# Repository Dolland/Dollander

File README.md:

# Handheld Gaming Console - Master Degree Thesis

As for the title, this project is my Electronics Engineering Master Thesis.
This is a handheld console based on Raspberry Pi Zero 2.

## HOW IT BEGAN

I started working on this idea some years ago and came up designing a console like in the photo:

*FOTO*

As you can see, this was a serious wires mess, but it worked! (actually it still works)
For the first prototipe I used ready-to-use boards for supply, audio, ADC and so on.
The screen was a Composite 5" retro camera 12V display (really bad quality).
The shell was entirely designed from scratch.

## HOW IT BECAME

After a year of use, i decided that this project deserved more attention and started thinking about a custom PCB that would integrate all the components needed for power supply, audio amplification, ADC, display driving etc.
I've designed the PMIC stage, as well as the display interfacing and all the other stuffs.
The PCB finally come out like this:

The console now has a 5" RGB Parallel Interface display driven by a HDMI-to-TTL converter that receives the HDMI signal from a HDMI switch, that in turn manages to switch the output between the internal display and the HDMI external port.

The console has an analog stick, 4 dorsal buttons, 14 front buttons, a speaker (but the PCB supports two speakers), a full-size HDMI output port, a USB-C charging port and a plenty of internal space for Li-Ion cells (i use a 3000mAh one but you can use bigger ones).

This project is by all means not perfect, some things are missing (backlight adjustment is supported by hardware but not implemented in the PCB) and surely the next PCB revision will be more compact (and so cheaper to order) but it works really well.

The design of the shell and the buttons was done in TinkerCAD (what an awful choice) because well, i only know this tool, but surely the next step should be porting all the CAD files into a more professional CAD (Fusion?)

Here is the top printing:

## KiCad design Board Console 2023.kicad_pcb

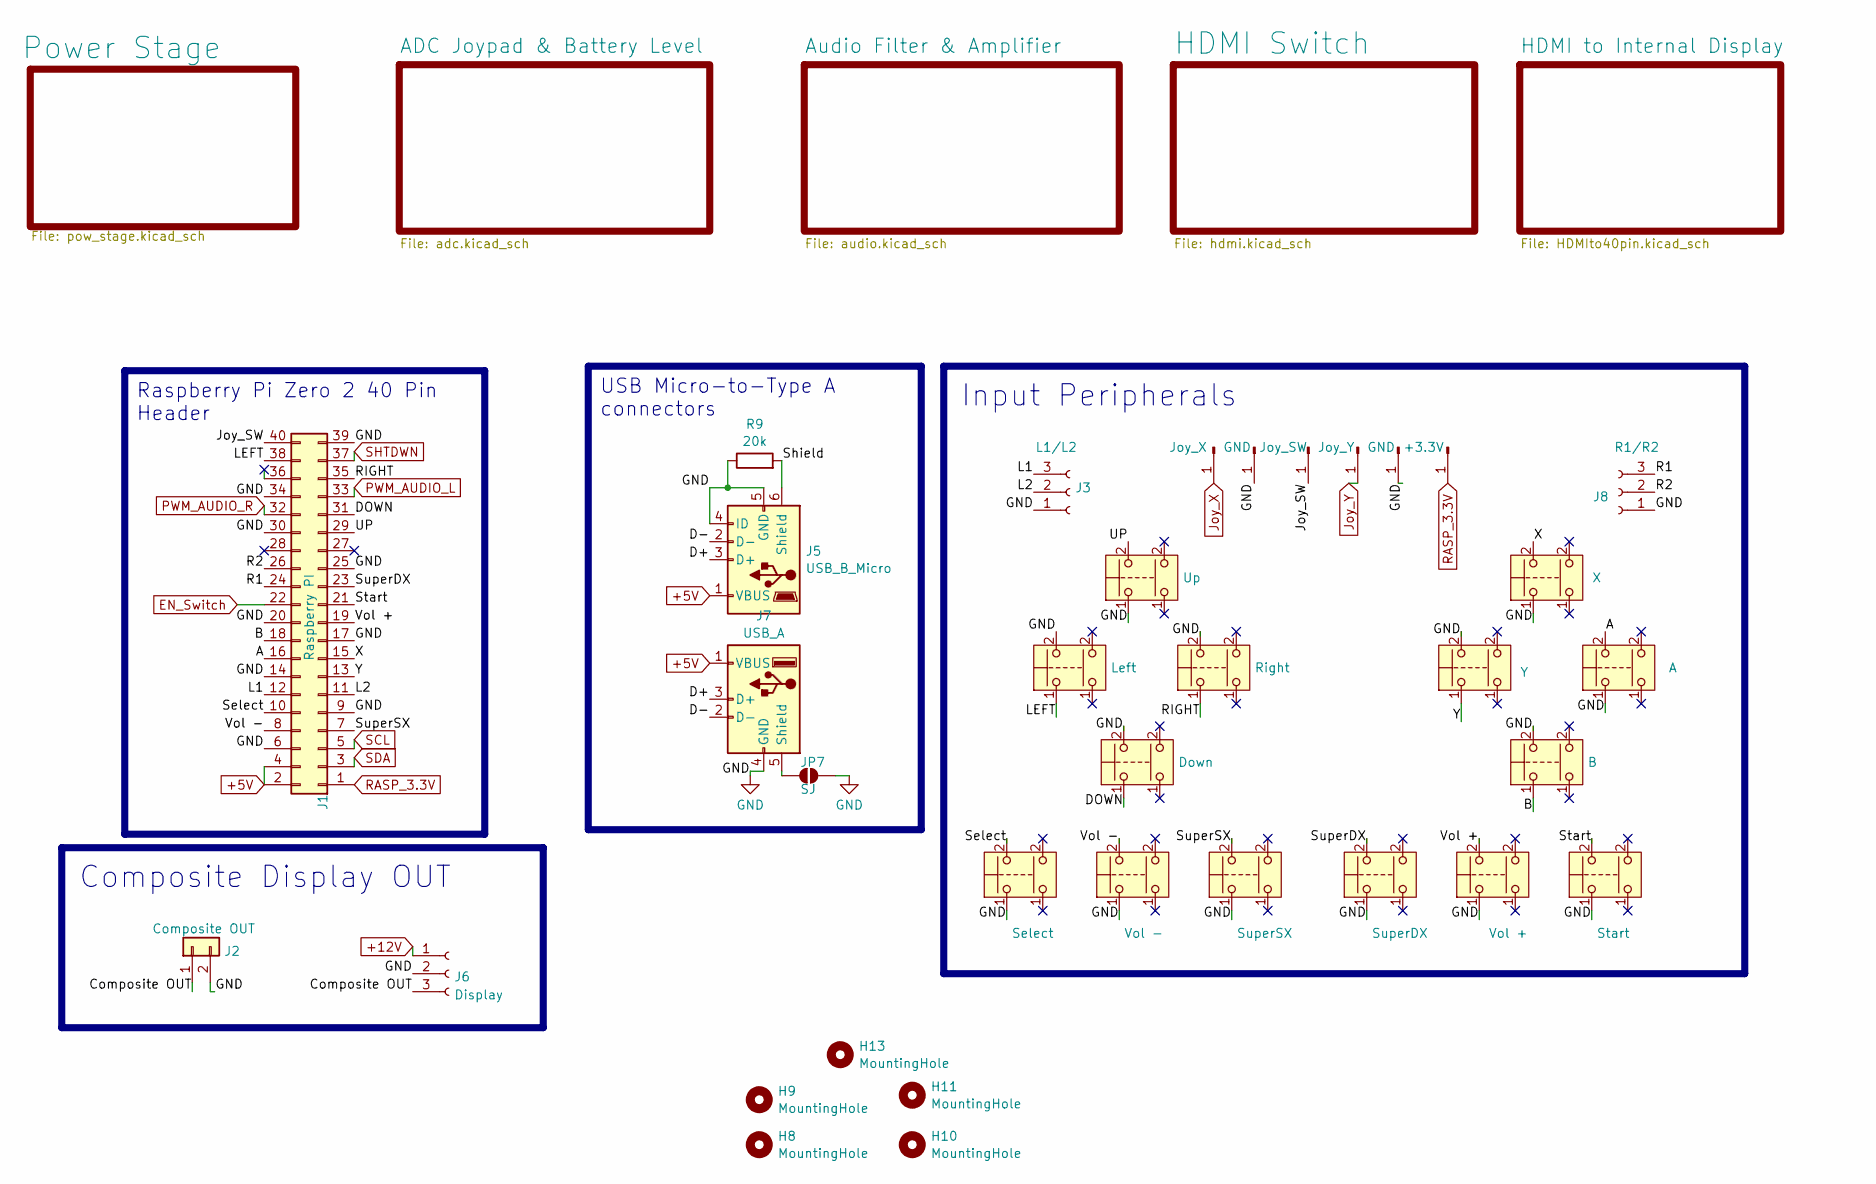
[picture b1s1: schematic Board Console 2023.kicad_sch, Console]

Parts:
H1: Joy_X; TestPoint_Pad_0.8x2.8
H2, H5: GND; TestPoint_Pad_0.8x2.8
H3: Joy_SW; TestPoint_Pad_0.8x2.8
H4: Joy_Y; TestPoint_Pad_0.8x2.8
H6: +3.3V; TestPoint_Pad_0.8x2.8
H8, H9, H10, H11, H13: MountingHole; MountingHole_2.2mm_M2
J1: Raspberry PI; Raspberry_Pi_Zero_Socketed_THT_FaceUp_MountingHoles
J2: Composite OUT; PinHeader_1x02_P2.00mm_Vertical
J3: L1/L2; PinHeader_1x03_P2.54mm_Vertical
J5: USB_B_Micro; USB_Micro-B_Amphenol_10118194_Horizontal
J6: Display; PinHeader_1x03_P2.54mm_Vertical
J7: USB_A; AMPHENOL_UE27AC5410H
J8: R1/R2; PinHeader_1x03_P2.54mm_Vertical
JP7: SJ; SolderJumper-2_P1.3mm_Open_Pad1.0x1.5mm
R9: 20k; R_0603_1608Metric_Pad0.98x0.95mm_HandSolder
SW3: Vol -; SW_Push_1P1T_NO_6x6mm_H9.5mm
SW4: SuperSX; SW_Push_1P1T_NO_6x6mm_H9.5mm
SW5: Select; SW_Push_1P1T_NO_6x6mm_H9.5mm
SW6: Vol +; SW_Push_1P1T_NO_6x6mm_H9.5mm
SW7: Start; SW_Push_1P1T_NO_6x6mm_H9.5mm
SW8: B; SW_Push_1P1T_NO_6x6mm_H9.5mm
SW9: Y; SW_Push_1P1T_NO_6x6mm_H9.5mm
SW10: A; SW_Push_1P1T_NO_6x6mm_H9.5mm
SW11: X; SW_Push_1P1T_NO_6x6mm_H9.5mm
SW12: Down; SW_Push_1P1T_NO_6x6mm_H9.5mm
SW13: Left; SW_Push_1P1T_NO_6x6mm_H9.5mm
SW14: Up; SW_Push_1P1T_NO_6x6mm_H9.5mm
SW15: Right; SW_Push_1P1T_NO_6x6mm_H9.5mm
SW17: SuperDX; SW_Push_1P1T_NO_6x6mm_H9.5mm

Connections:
+5V: J1.2, J1.4, J5.1 (VBUS), J7.1 (VBUS); also elsewhere on the board
+12V: J6.1; also elsewhere on the board
/A: J1.16, SW10.2
/B: J1.18, SW8.1
/Composite OUT: J2.1, J6.3
/D+: J5.3 (D+), J7.3 (D+)
/D-: J5.2 (D-), J7.2 (D-)
/DOWN: J1.31, SW12.1
/Joy_SW: H3.1, J1.40
/L1: J1.12, J3.3
/L2: J1.11, J3.2
/LEFT: J1.38, SW13.1
/R1: J1.24, J8.3
/R2: J1.26, J8.2
/RIGHT: J1.35, SW15.1
/Select: J1.10, SW5.2
/Shield: J5.6 (Shield), R9.2
/Start: J1.21, SW7.2
/SuperDX: J1.23, SW17.2
/SuperSX: J1.7, SW4.2
/UP: J1.29, SW14.2
/Vol +: J1.19, SW6.2
/Vol -: J1.8, SW3.2
/X: J1.15, SW11.2
/Y: J1.13, SW9.1
EN_Switch: J1.22; also elsewhere on the board
GND: H2.1, H5.1, J1.6, J1.9, J1.14, J1.17, J1.20, J1.25, J1.30, J1.34, J1.39, J2.2, J3.1, J5.4 (ID), J5.5 (GND), J6.2, J7.4 (GND), J8.1, JP7.1 (A), R9.1, SW3.1, SW4.1, SW5.1, SW6.1, SW7.1, SW8.2, SW9.2, SW10.1, SW11.1, SW12.2, SW13.2, SW14.1, SW15.2, SW17.1; also elsewhere on the board
Joy_X: H1.1; also elsewhere on the board
Joy_Y: H4.1; also elsewhere on the board
unnamed: J7.5 (Shield), JP7.2 (B)
PWM_AUDIO_L: J1.33; also elsewhere on the board
PWM_AUDIO_R: J1.32; also elsewhere on the board
RASP_3.3V: H6.1, J1.1; also elsewhere on the board
SCL: J1.5; also elsewhere on the board
SDA: J1.3; also elsewhere on the board
SHTDWN: J1.37; also elsewhere on the board

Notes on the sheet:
Composite Display OUT
Raspberry Pi Zero 2 40 Pin Header
USB Micro-to-Type A connectors
Input Peripherals

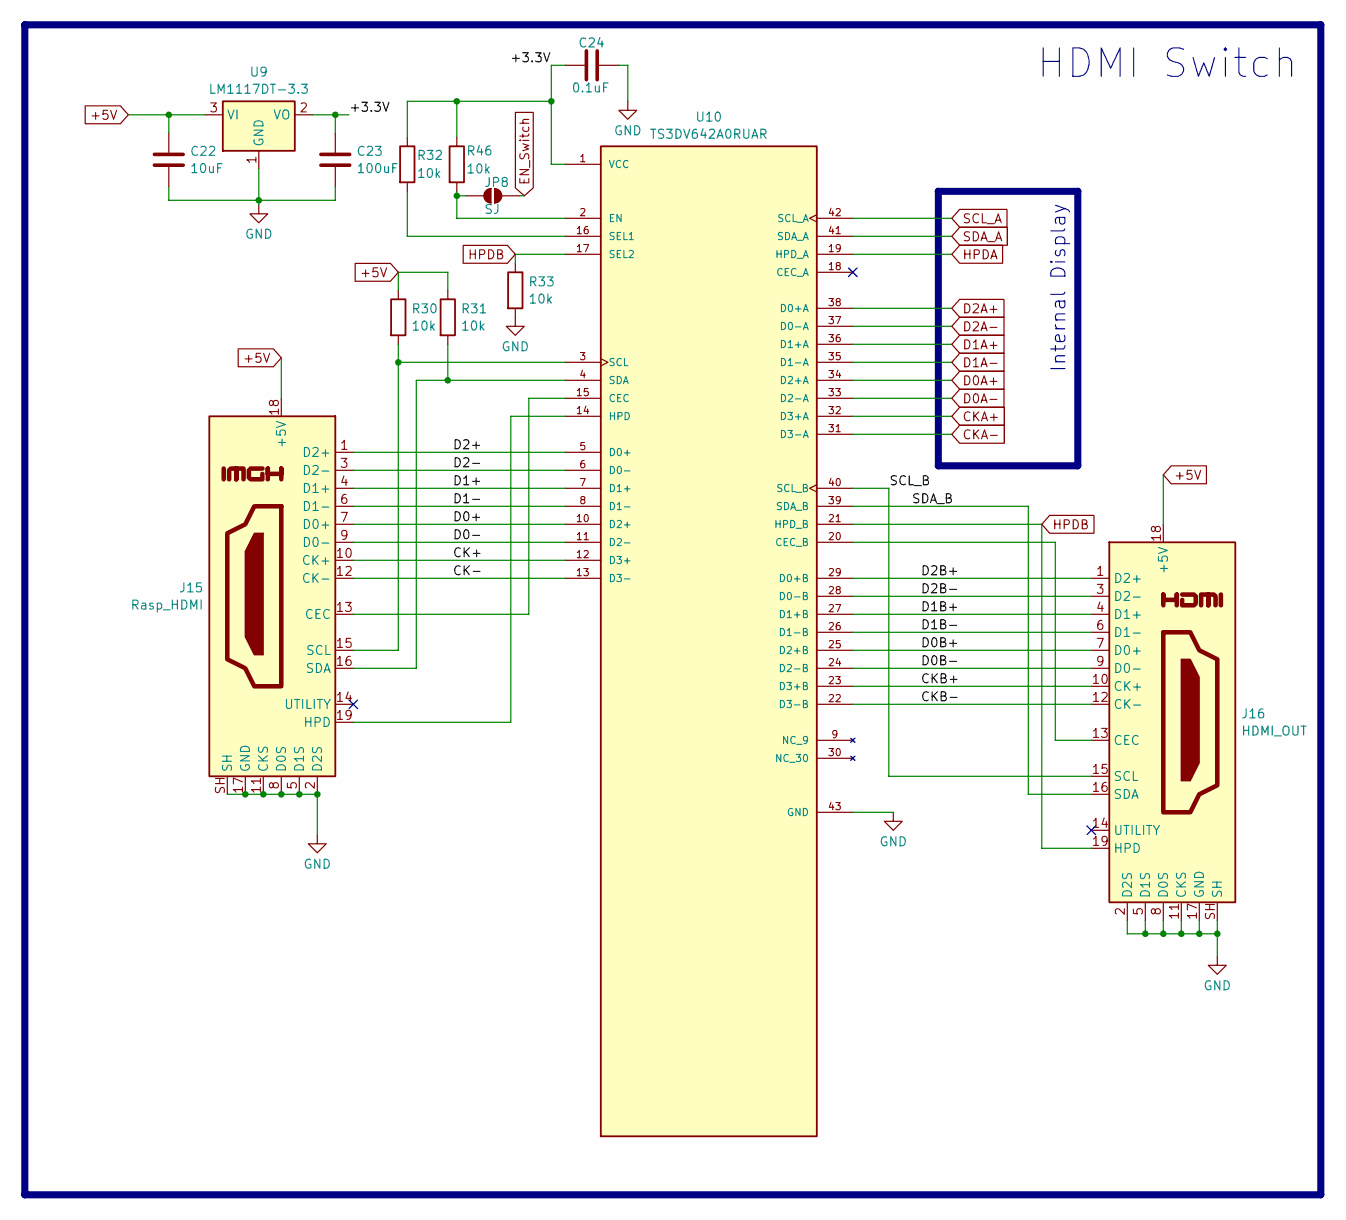
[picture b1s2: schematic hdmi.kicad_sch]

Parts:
C22: 10uF; C_0603_1608Metric_Pad1.08x0.95mm_HandSolder
C23: 100uF; C_1206_3216Metric_Pad1.33x1.80mm_HandSolder
C24: 0.1uF; C_0603_1608Metric_Pad1.08x0.95mm_HandSolder
J15: Rasp_HDMI; HDMI_A_Amphenol_10029449-x01xLF_Horizontal
J16: HDMI_OUT; HDMI_A_Amphenol_10029449-x01xLF_Horizontal
JP8: SJ; SolderJumper-2_P1.3mm_Open_Pad1.0x1.5mm
R30, R31, R32, R33, R46: 10k; R_0603_1608Metric_Pad0.98x0.95mm_HandSolder
U9: LM1117DT-3.3; SOT-223-3_TabPin2
U10: TS3DV642A0RUAR; QFN50P900X350X80-43N; PARTREV 4219139/A 03/2020

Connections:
+5V: C22.1, J15.18 (+5V), J16.18 (+5V), R30.1, R31.1, U9.3 (VI); also elsewhere on the board
/HDMI Switch/+3.3V: C23.1, C24.1, R32.1, R46.1, U9.2 (VO), U10.1 (VCC)
/HDMI Switch/CK+: J15.10 (CK+), U10.12 (D3+)
/HDMI Switch/CK-: J15.12 (CK-), U10.13 (D3-)
/HDMI Switch/CKB+: J16.10 (CK+), U10.23 (D3+B)
/HDMI Switch/CKB-: J16.12 (CK-), U10.22 (D3-B)
/HDMI Switch/D0+: J15.7 (D0+), U10.10 (D2+)
/HDMI Switch/D0-: J15.9 (D0-), U10.11 (D2-)
/HDMI Switch/D0B+: J16.7 (D0+), U10.25 (D2+B)
/HDMI Switch/D0B-: J16.9 (D0-), U10.24 (D2-B)
/HDMI Switch/D1+: J15.4 (D1+), U10.7 (D1+)
/HDMI Switch/D1-: J15.6 (D1-), U10.8 (D1-)
/HDMI Switch/D1B+: J16.4 (D1+), U10.27 (D1+B)
/HDMI Switch/D1B-: J16.6 (D1-), U10.26 (D1-B)
/HDMI Switch/D2+: J15.1 (D2+), U10.5 (D0+)
/HDMI Switch/D2-: J15.3 (D2-), U10.6 (D0-)
/HDMI Switch/D2B+: J16.1 (D2+), U10.29 (D0+B)
/HDMI Switch/D2B-: J16.3 (D2-), U10.28 (D0-B)
/HDMI Switch/SCL_B: J16.15 (SCL), U10.40 (SCL_B)
/HDMI Switch/SDA_B: J16.16 (SDA), U10.39 (SDA_B)
CKA+: U10.32 (D3+A); also elsewhere on the board
CKA-: U10.31 (D3-A); also elsewhere on the board
D0A+: U10.34 (D2+A); also elsewhere on the board
D0A-: U10.33 (D2-A); also elsewhere on the board
D1A+: U10.36 (D1+A); also elsewhere on the board
D1A-: U10.35 (D1-A); also elsewhere on the board
D2A+: U10.38 (D0+A); also elsewhere on the board
D2A-: U10.37 (D0-A); also elsewhere on the board
EN_Switch: JP8.1 (A); also elsewhere on the board
GND: C22.2, C23.2, C24.2, J15.2 (D2S), J15.5 (D1S), J15.8 (D0S), J15.11 (CKS), J15.17 (GND), J15.SH, J16.2 (D2S), J16.5 (D1S), J16.8 (D0S), J16.11 (CKS), J16.17 (GND), J16.SH, R33.2, U9.1 (GND), U10.43 (GND); also elsewhere on the board
HPDA: U10.19 (HPD_A); also elsewhere on the board
HPDB: J16.19 (HPD), R33.1, U10.17 (SEL2), U10.21 (HPD_B)
unnamed: J15.13 (CEC), U10.15 (CEC)
unnamed: J15.19 (HPD), U10.14 (HPD)
unnamed: J15.15 (SCL), R30.2, U10.3 (SCL)
unnamed: J15.16 (SDA), R31.2, U10.4 (SDA)
unnamed: J16.13 (CEC), U10.20 (CEC_B)
unnamed: JP8.2 (B), R46.2, U10.2 (EN)
unnamed: R32.2, U10.16 (SEL1)
SCL_A: U10.42 (SCL_A); also elsewhere on the board
SDA_A: U10.41 (SDA_A); also elsewhere on the board

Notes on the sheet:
Internal Display
HDMI Switch

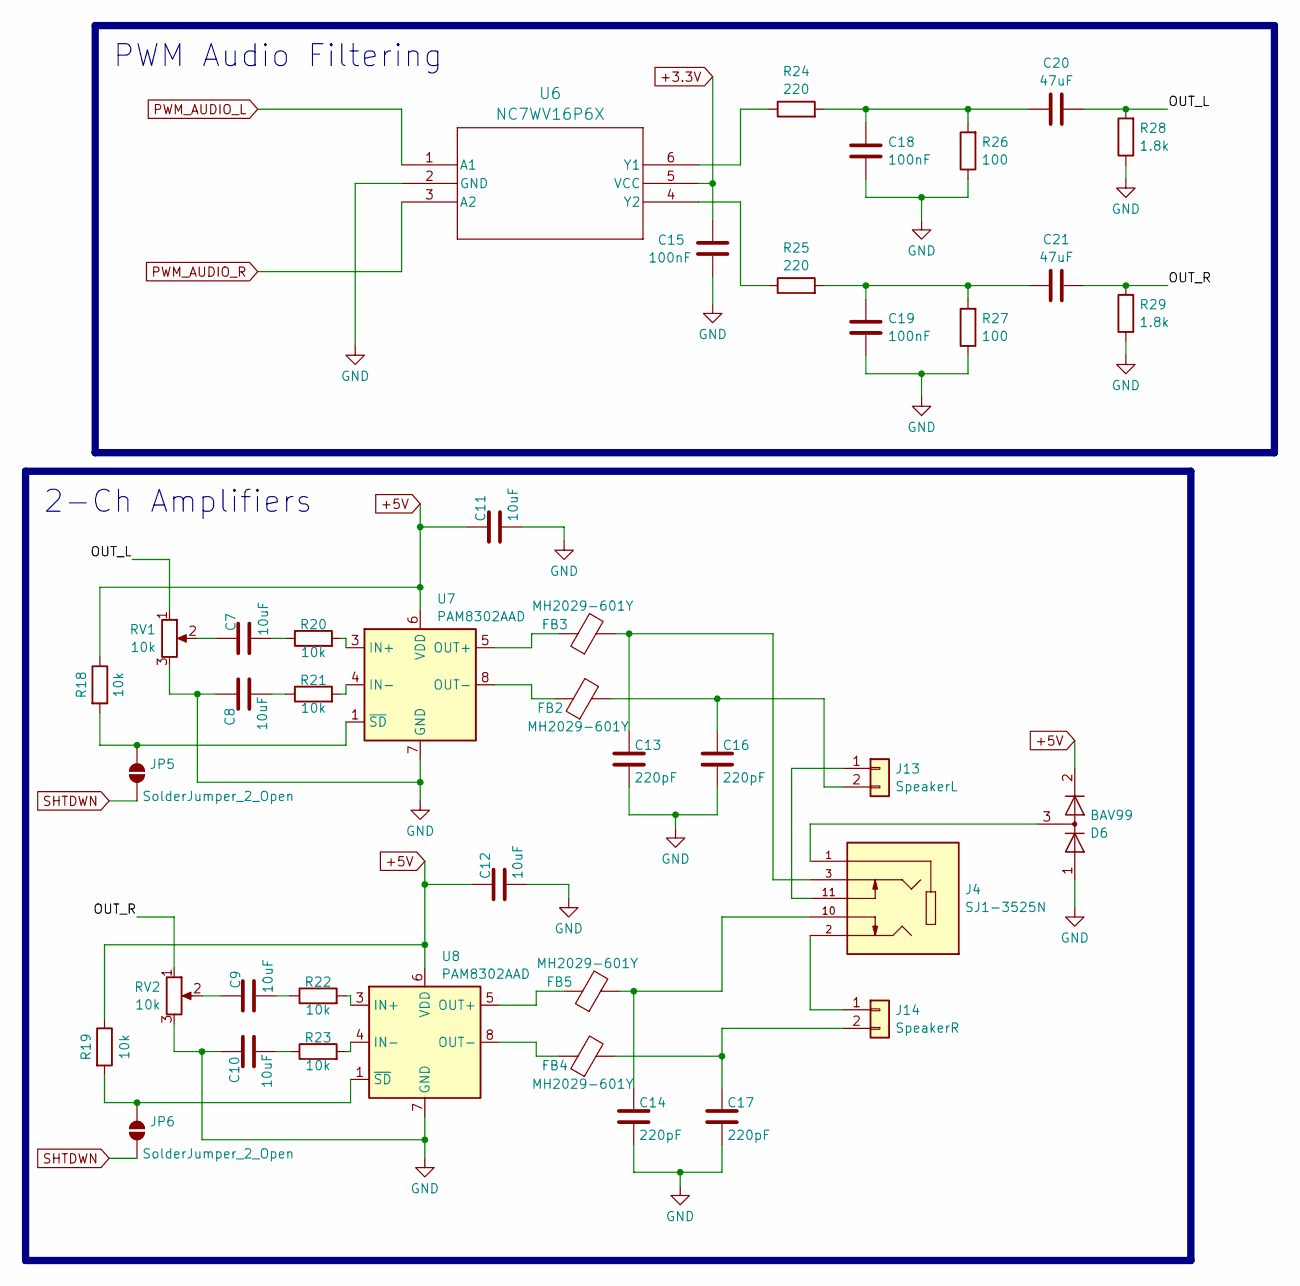
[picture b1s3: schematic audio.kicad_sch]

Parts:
C7, C8, C9, C10, C11, C12: 10uF; C_0603_1608Metric_Pad1.08x0.95mm_HandSolder
C13, C14, C16, C17: 220pF; C_0603_1608Metric_Pad1.08x0.95mm_HandSolder
C15, C18, C19: 100nF; C_0603_1608Metric_Pad1.08x0.95mm_HandSolder
C20, C21: 47uF; C_1206_3216Metric_Pad1.33x1.80mm_HandSolder
D6: BAV99; SOT-23
FB2, FB3, FB4, FB5: MH2029-601Y; L_0805_2012Metric_Pad1.05x1.20mm_HandSolder
J4: SJ1-3525N; CUI_SJ1-3525N; PARTREV 1.05
J13: SpeakerL; PinHeader_1x02_P2.54mm_Vertical
J14: SpeakerR; PinHeader_1x02_P2.54mm_Vertical
JP5, JP6: SolderJumper_2_Open; SolderJumper-2_P1.3mm_Open_Pad1.0x1.5mm
R18, R19, R20, R21, R22, R23: 10k; R_0603_1608Metric_Pad0.98x0.95mm_HandSolder
R24, R25: 220; R_0603_1608Metric_Pad0.98x0.95mm_HandSolder
R26, R27: 100; R_0603_1608Metric_Pad0.98x0.95mm_HandSolder
R28, R29: 1.8k; R_0603_1608Metric_Pad0.98x0.95mm_HandSolder
RV1, RV2: 10k; Potentiometer_Bourns_TC33X_Vertical
U6: NC7WV16P6X; SC70-6_2P2X1P35_ONS
U7, U8: PAM8302AAD; PAM8302AASCR_DIO

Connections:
+3.3V: C15.2, U6.5 (VCC); also elsewhere on the board
+5V: C11.1, C12.1, D6.2 (A), R18.1, R19.1, U7.6 (VDD), U8.6 (VDD); also elsewhere on the board
/Audio Filter & Amplifier/OUT_L: C20.2, R28.2, RV1.1
/Audio Filter & Amplifier/OUT_R: C21.2, R29.2, RV2.1
GND: C8.1, C10.1, C11.2, C12.2, C13.2, C14.2, C15.1, C16.2, C17.2, C18.2, C19.2, D6.1 (K), R26.1, R27.1, R28.1, R29.1, RV1.3, RV2.3, U6.2 (GND), U7.7 (GND), U8.7 (GND); also elsewhere on the board
unnamed: C7.1, RV1.2
unnamed: C7.2, R20.1
unnamed: C8.2, R21.1
unnamed: C9.1, RV2.2
unnamed: C9.2, R22.1
unnamed: C10.2, R23.1
unnamed: C13.1, FB3.2, J4.3
unnamed: C14.1, FB5.2, J4.10
unnamed: C18.1, C20.1, R24.2, R26.2
unnamed: C19.1, C21.1, R25.2, R27.2
unnamed: D6.3 (K), J4.1
unnamed: J4.11, J13.1
unnamed: C16.1, FB2.2, J13.2
unnamed: J4.2, J14.1
unnamed: C17.1, FB4.2, J14.2
unnamed: JP5.2 (B), R18.2, U7.1 (~SD)
unnamed: JP6.2 (B), R19.2, U8.1 (~SD)
unnamed: R24.1, U6.6 (Y1)
unnamed: R25.1, U6.4 (Y2)
unnamed: R20.2, U7.3 (IN+)
unnamed: R21.2, U7.4 (IN-)
unnamed: FB3.1, U7.5 (OUT+)
unnamed: FB2.1, U7.8 (OUT-)
unnamed: R22.2, U8.3 (IN+)
unnamed: R23.2, U8.4 (IN-)
unnamed: FB5.1, U8.5 (OUT+)
unnamed: FB4.1, U8.8 (OUT-)
PWM_AUDIO_L: U6.1 (A1); also elsewhere on the board
PWM_AUDIO_R: U6.3 (A2); also elsewhere on the board
SHTDWN: JP5.1 (A), JP6.1 (A); also elsewhere on the board

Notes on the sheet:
PWM Audio Filtering
2-Ch Amplifiers

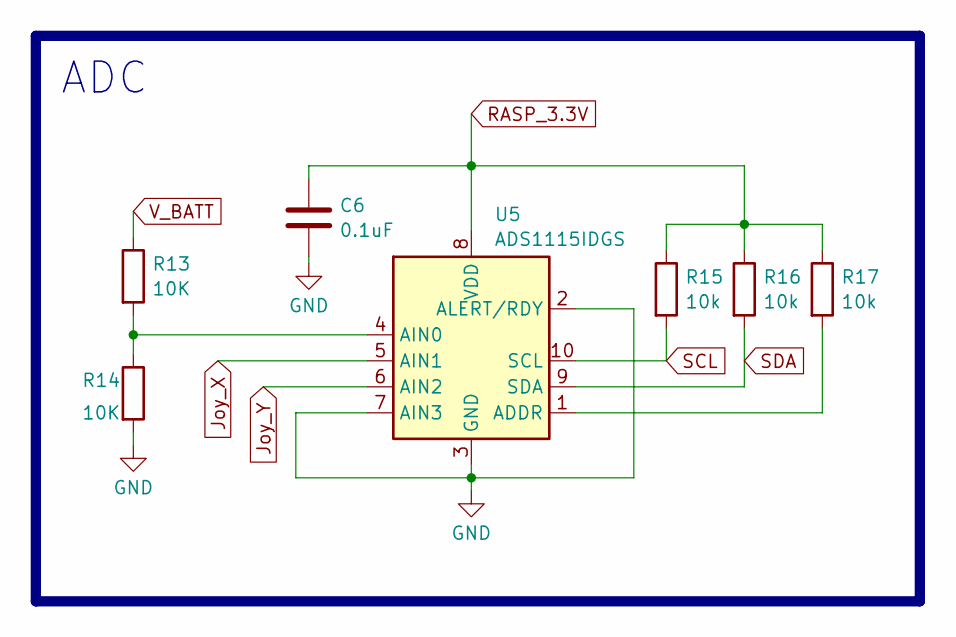
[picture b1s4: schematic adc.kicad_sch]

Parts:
C6: 0.1uF; C_0603_1608Metric_Pad1.08x0.95mm_HandSolder
R13, R14: 10K; R_0603_1608Metric_Pad0.98x0.95mm_HandSolder
R15, R16, R17: 10k; R_0603_1608Metric_Pad0.98x0.95mm_HandSolder
U5: ADS1115IDGS; TSSOP-10_3x3mm_P0.5mm

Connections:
GND: C6.2, R14.2, U5.2 (ALERT/RDY), U5.3 (GND), U5.7 (AIN3); also elsewhere on the board
Joy_X: U5.5 (AIN1); also elsewhere on the board
Joy_Y: U5.6 (AIN2); also elsewhere on the board
unnamed: R17.2, U5.1 (ADDR)
unnamed: R13.2, R14.1, U5.4 (AIN0)
RASP_3.3V: C6.1, R15.1, R16.1, R17.1, U5.8 (VDD); also elsewhere on the board
SCL: R15.2, U5.10 (SCL); also elsewhere on the board
SDA: R16.2, U5.9 (SDA); also elsewhere on the board
V_BATT: R13.1; also elsewhere on the board

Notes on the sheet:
ADC

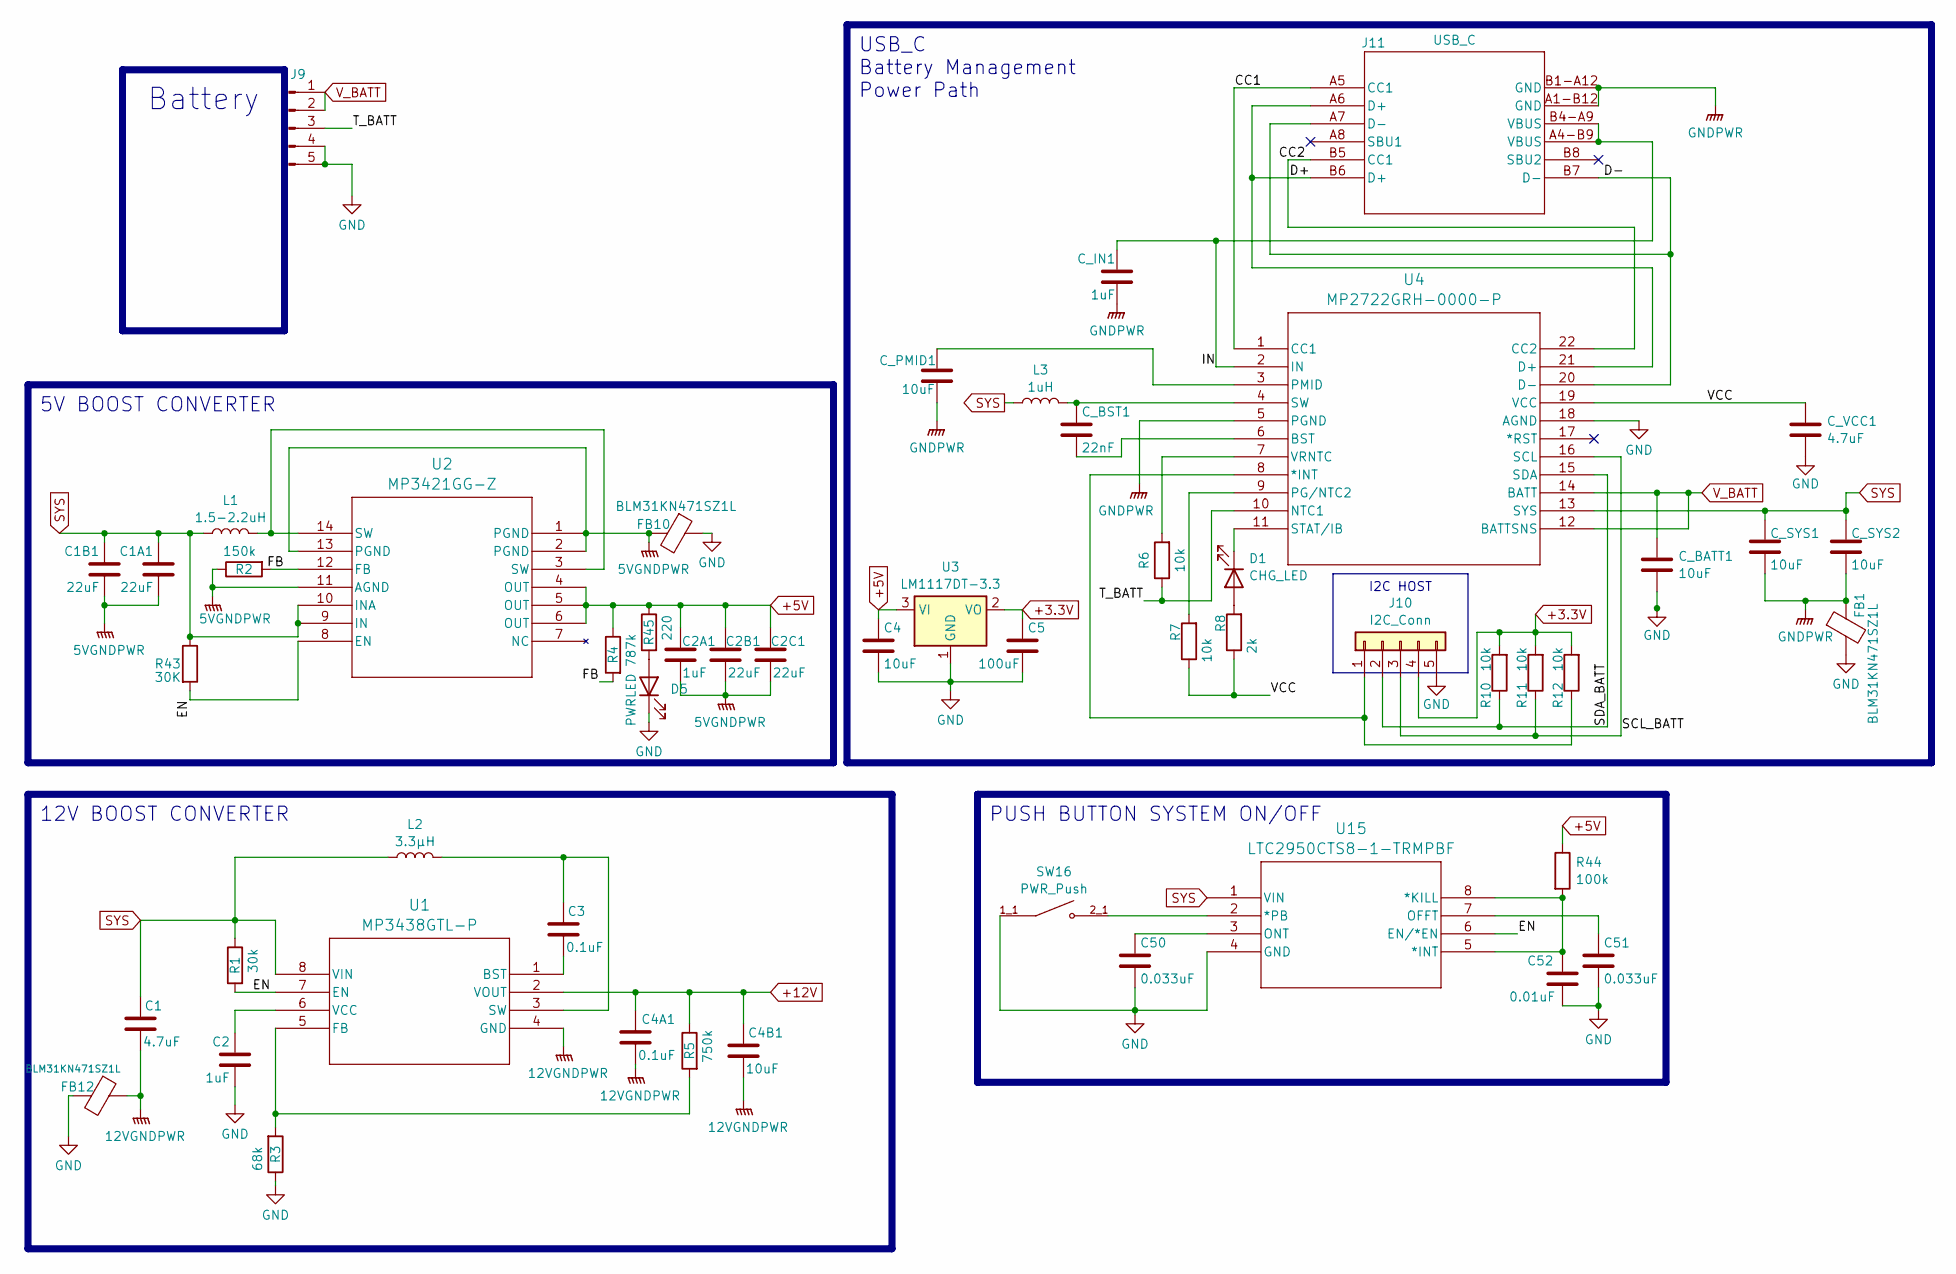
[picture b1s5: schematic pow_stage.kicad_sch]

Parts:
C1: 4.7uF; C_1206_3216Metric_Pad1.33x1.80mm_HandSolder
C1A1, C1B1, C2B1, C2C1: 22uF; C_1206_3216Metric_Pad1.33x1.80mm_HandSolder
C2, C2A1: 1uF; C_0603_1608Metric_Pad1.08x0.95mm_HandSolder
C3, C4A1: 0.1uF; C_0603_1608Metric_Pad1.08x0.95mm_HandSolder
C4: 10uF; C_0603_1608Metric_Pad1.08x0.95mm_HandSolder
C4B1: 10uF; C_1206_3216Metric_Pad1.33x1.80mm_HandSolder
C5: 100uF; C_1206_3216Metric_Pad1.33x1.80mm_HandSolder
C50, C51: 0.033uF; C_0603_1608Metric_Pad1.08x0.95mm_HandSolder
C52: 0.01uF; C_0603_1608Metric_Pad1.08x0.95mm_HandSolder
C_BATT1: 10uF; C_0805_2012Metric_Pad1.18x1.45mm_HandSolder
C_BST1: 22nF; C_0603_1608Metric_Pad1.08x0.95mm_HandSolder
C_IN1: 1uF; C_0603_1608Metric_Pad1.08x0.95mm_HandSolder
C_PMID1: 10uF; C_0805_2012Metric_Pad1.18x1.45mm_HandSolder
C_SYS1, C_SYS2: 10uF; C_0805_2012Metric_Pad1.18x1.45mm_HandSolder
C_VCC1: 4.7uF; C_0603_1608Metric_Pad1.08x0.95mm_HandSolder
D1: CHG_LED; LED_D1.8mm_W1.8mm_H2.4mm_Horizontal_O1.27mm_Z1.6mm
D5: PWRLED; LED_D1.8mm_W1.8mm_H2.4mm_Horizontal_O1.27mm_Z1.6mm
FB1, FB10, FB12: BLM31KN471SZ1L; L_1206_3216Metric_Pad1.22x1.90mm_HandSolder
J9: V_BATT; PinHeader_1x05_P2.54mm_Vertical
J10: I2C_Conn; PinHeader_1x05_P2.00mm_Vertical
J11: USB_C; 12402012E212A_AMP
L1: 1.5-2.2uH; L_Bourns_SRN6045TA
L2: 3.3µH; L_Vishay_IFSC-1515AH_4x4x1.8mm
L3: 1uH; L_Bourns_SRP5030T
R1: 30k; R_0603_1608Metric_Pad0.98x0.95mm_HandSolder
R2: 150k; R_0603_1608Metric_Pad0.98x0.95mm_HandSolder
R3: 68k; R_0603_1608Metric_Pad0.98x0.95mm_HandSolder
R4: 787k; R_0603_1608Metric_Pad0.98x0.95mm_HandSolder
R5: 750k; R_0603_1608Metric_Pad0.98x0.95mm_HandSolder
R6, R7, R10, R11, R12: 10k; R_0603_1608Metric_Pad0.98x0.95mm_HandSolder
R8: 2k; R_0603_1608Metric_Pad0.98x0.95mm_HandSolder
R43: 30K; R_0603_1608Metric_Pad0.98x0.95mm_HandSolder
R44: 100k; R_0603_1608Metric_Pad0.98x0.95mm_HandSolder
R45: 220; R_0603_1608Metric_Pad0.98x0.95mm_HandSolder
SW16: PWR_Push; SW_EVQ-P7A01P; PARTREV 2022.4
U1: MP3438GTL-P; SOT583_MP3438_MNP
U2: MP3421GG-Z; QFN-14_MP3421_MNP
U3: LM1117DT-3.3; SOT-223-3_TabPin2
U4: MP2722GRH-0000-P; QFN-22_MP2722_MNP
U15: LTC2950CTS8-1-TRMPBF; TSOT-23_TS8_LIT

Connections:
5VGNDPWR: C1A1.2, C1B1.2, C2A1.2, C2B1.2, C2C1.2, FB10.2, R2.1, U2.1 (PGND), U2.2 (PGND), U2.11 (AGND), U2.13 (PGND)
12VGNDPWR: C1.2, C4A1.2, C4B1.2, FB12.1, U1.4 (GND)
+3.3V: C5.1, J10.4, R10.2, R11.2, R12.2, U3.2 (VO); also elsewhere on the board
+5V: C2A1.1, C2B1.1, C2C1.1, C4.1, R4.1, R44.1, R45.1, U2.4 (OUT), U2.5 (OUT), U2.6 (OUT), U3.3 (VI); also elsewhere on the board
+12V: C4A1.1, C4B1.1, R5.1, U1.2 (VOUT); also elsewhere on the board
/Power Stage/CC1: J11.A5 (CC1), U4.1 (CC1)
/Power Stage/CC2: J11.B5 (CC1), U4.22 (CC2)
/Power Stage/D+: J11.A6 (D+), J11.B6 (D+), U4.21 (D+)
/Power Stage/D-: J11.A7 (D-), J11.B7 (D-), U4.20 (D-)
/Power Stage/EN: R1.2, R43.2, U1.7 (EN), U2.8 (EN), U15.6 (EN/*EN)
/Power Stage/FB: R2.2, R4.2, U2.12 (FB)
/Power Stage/IN: C_IN1.1, J11.A4-B9 (VBUS), J11.B4-A9 (VBUS), U4.2 (IN)
/Power Stage/SCL_BATT: J10.3, R11.1, U4.16 (SCL)
/Power Stage/SDA_BATT: J10.2, R10.1, U4.15 (SDA)
/Power Stage/T_BATT: J9.3, R6.1, U4.10 (NTC1)
/Power Stage/VCC: C_VCC1.1, R7.1, R8.1, U4.19 (VCC)
GND: C2.2, C4.2, C5.2, C50.2, C51.2, C52.2, C_BATT1.2, C_VCC1.2, D5.1 (K), FB1.2, FB10.1, FB12.2, J9.4, J9.5, J10.5, R3.1, SW16.1_1, U3.1 (GND), U4.18 (AGND), U15.4 (GND); also elsewhere on the board
GNDPWR: C_IN1.2, C_PMID1.2, C_SYS1.2, C_SYS2.2, FB1.1, J11.A1-B12 (GND), J11.B1-A12 (GND), U4.5 (PGND)
unnamed: D1.2 (A), R8.2
unnamed: D1.1 (K), U4.11 (STAT/IB)
unnamed: D5.2 (A), R45.2
unnamed: J10.1, R12.1, U4.8 (*INT)
unnamed: L1.1, U2.3 (SW), U2.14 (SW)
unnamed: C3.2, U1.1 (BST)
unnamed: R3.2, R5.2, U1.5 (FB)
unnamed: C3.1, L2.1, U1.3 (SW)
unnamed: C2.1, U1.6 (VCC)
unnamed: C_BST1.2, U4.6 (BST)
unnamed: R7.2, U4.9 (PG/NTC2)
unnamed: C_PMID1.1, U4.3 (PMID)
unnamed: C_BST1.1, L3.2, U4.4 (SW)
unnamed: R6.2, U4.7 (VRNTC)
unnamed: C52.1, R44.2, U15.5 (*INT), U15.8 (*KILL)
unnamed: SW16.2_1, U15.2 (*PB)
unnamed: C51.1, U15.7 (OFFT)
unnamed: C50.1, U15.3 (ONT)
SYS: C1.1, C1A1.1, C1B1.1, C_SYS1.1, C_SYS2.1, L1.2, L2.2, L3.1, R1.1, R43.1, U1.8 (VIN), U2.9 (IN), U2.10 (INA), U4.13 (SYS), U15.1 (VIN)
V_BATT: C_BATT1.1, J9.1, J9.2, U4.12 (BATTSNS), U4.14 (BATT); also elsewhere on the board

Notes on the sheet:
PUSH BUTTON SYSTEM ON/OFF
5V BOOST CONVERTER
I2C HOST
12V BOOST CONVERTER
Battery
USB_C Battery Management Power Path
